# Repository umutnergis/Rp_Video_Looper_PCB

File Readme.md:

# Raspberry Pi Kart Okuma ve Video Oynatma Projesi

Bu proje, Raspberry Pi kullanarak bir kart okuma cihazı USB içinde money.txt klasöründeki int değeri kadar algılandığında USB üzerindeki bir videoyu oynatmayı ve bir fanın çalışmasını kontrol etmeyi amaçlar. Bu README dosyası, projenin nasıl kurulacağı, yapılandırılacağı ve kullanılacağı hakkında temel bilgileri içerir.

## Raspberry Pi için Gereksinimler

Bu projeyi başlatmak için aşağıdaki bileşenlere ihtiyacınız olacak:

- Raspberry Pi (örneğin, Raspberry Pi 3 veya Raspberry Pi 4)
- Kart Okuyucu (USB)
- Fan
- Röle modülü veya sürücü devreleri
- Python 3.7

## Kurulum

1. Raspberry Pi'nizi ağa bağlayın ve gerekli güncellemeleri yapmak için bir terminal açın:

   ```shell
   sudo apt update
   sudo apt upgrade

2. Main.py dosyasını Raspberry Pi'nize yükleyin. 

3. Eğer Raspberry pi'nızda otomatik başlatmak istiyorsanız AutoStart klasöründeki dosyayı inceleyebilirsiniz.

## Raspberry Pi PCB için Gereksinimler

- PCB dosyası Raspberry pi 1B için tasarlanmıştır.
<<<<<<< HEAD

##                                                FOR ENGLİSH

## Raspberry Pi Card Reading and Video Playback Project
 This project aims to use a Raspberry Pi to read a card reader device plugged into a USB port and, when an integer value is detected in the money.txt folder on the USB, play a video from the USB and control the operation of a fan. This README file contains basic information on how to set up, configure, and use the project.

## Requirements for Raspberry Pi
- To start this project, you will need the following components:

## Raspberry Pi (e.g., Raspberry Pi 3 or Raspberry Pi 4)
- Card Reader (USB)
- Fan
- Relay module or driver circuits
- Python 3.7
- Installation

1. Connect your Raspberry Pi to the network and open a terminal to perform the necessary updates:

   ```shell
   sudo apt update
   sudo apt upgrade

2. Upload the Main.py file to your Raspberry Pi.

3. If you want to auto-start the project on your Raspberry Pi, you can review the file in the AutoStart folder.

4. Place the files you want to load into your USB as first.mp4, second.mp4, and money.txt.

## Requirements for Raspberry Pi PCB
- The PCB file is designed for Raspberry Pi 1B.
- KiCAD 7.0 was used for design.
- The required footprints and schematics are available in the "Rp_project_requirements" file.
=======
- KICAD 7.0 kullanılmıştır.
- Gerekli olan footprint ve schematicler "Rp_project_reguirements" dosyasında yüklenmiştir.

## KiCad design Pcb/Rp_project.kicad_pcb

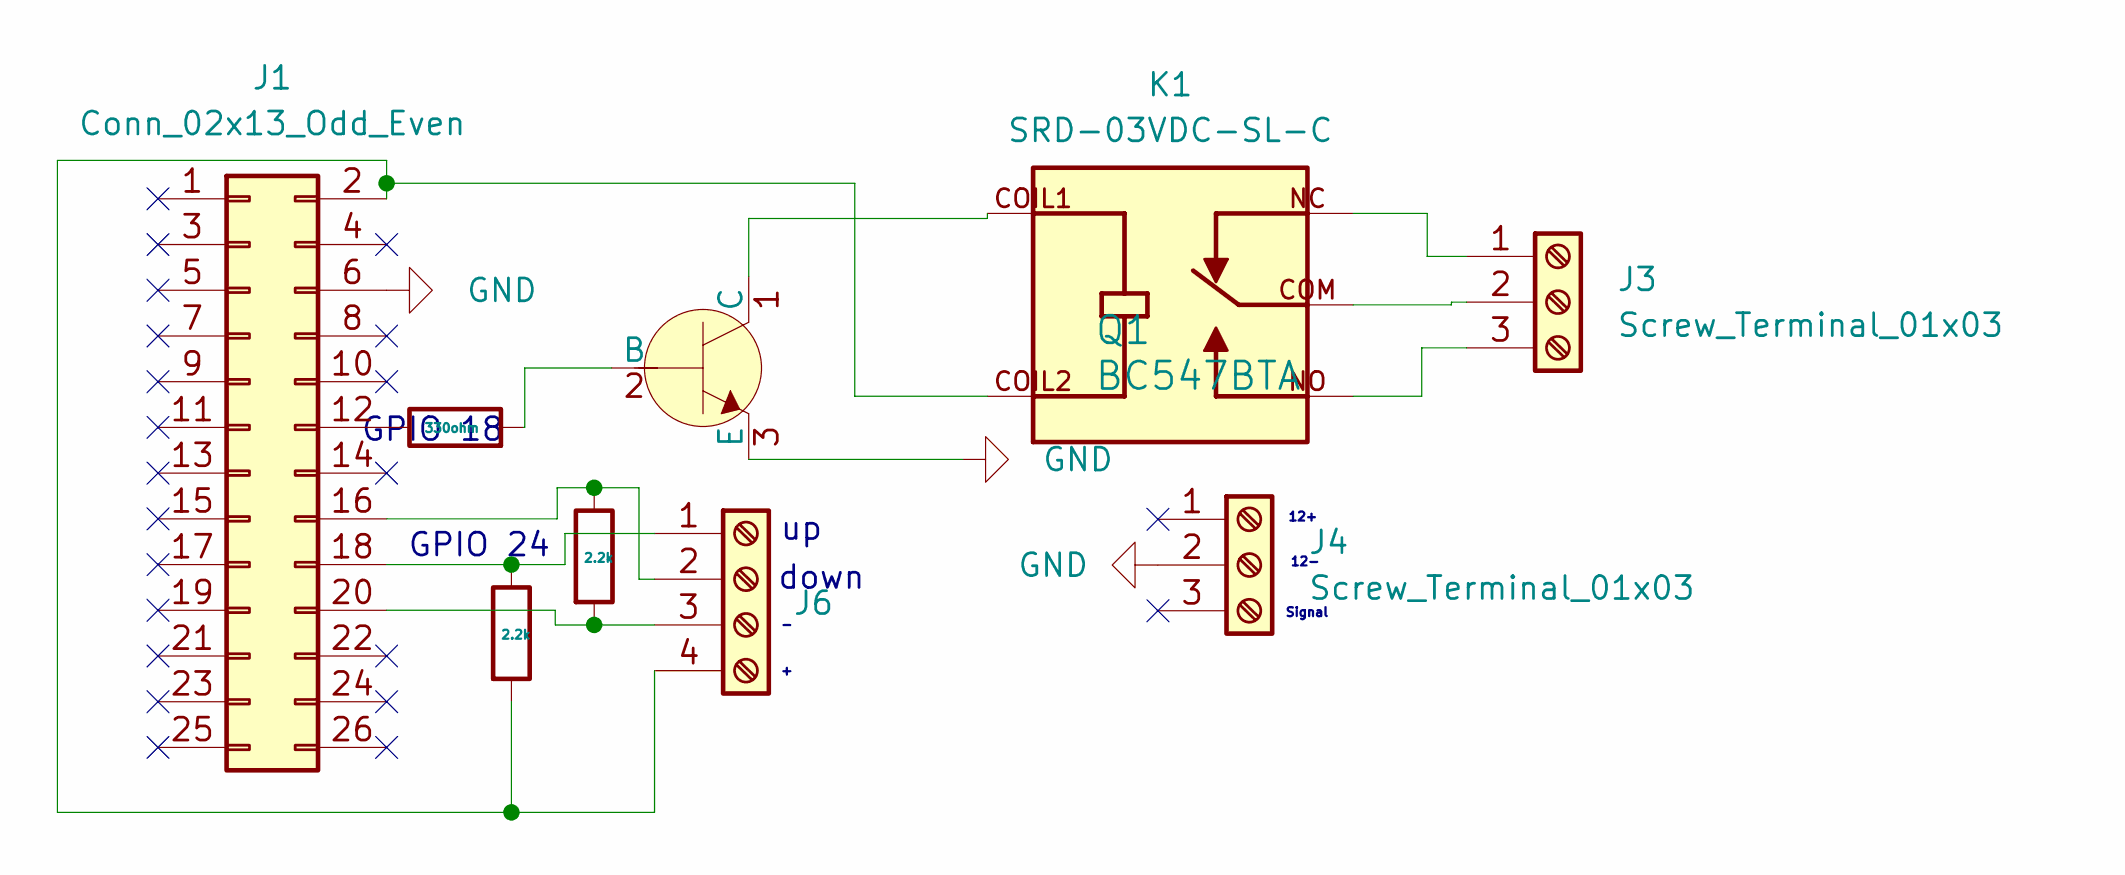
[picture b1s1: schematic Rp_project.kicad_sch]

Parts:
J1: Conn_02x13_Odd_Even; PinSocket_2x13_P2.54mm_Vertical
J3, J4: Screw_Terminal_01x03; TerminalBlock_RND_205-00046_1x03_P5.00mm_Horizontal
J6: Screw_Terminal_01x04; TerminalBlock_RND_205-00047_1x04_P5.00mm_Horizontal
K1: SRD-03VDC-SL-C; RELAY_SRD-03VDC-SL-C; PARTREV 20161104
Q1: BC547BTA; TO-92-3_Formed_Leads; MPN BC547BTA; Digi-Key_PN BC547BTACT-ND
R1, R2: 2.2k; R_Axial_DIN0207_L6.3mm_D2.5mm_P15.24mm_Horizontal
R3: 330ohm; R_Axial_DIN0207_L6.3mm_D2.5mm_P15.24mm_Horizontal

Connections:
GND: J1.6, J4.2, Q1.3 (E)
unnamed: J1.2, J6.4, K1.COIL2, R1.2
unnamed: J1.12, R3.1
unnamed: J1.16, J6.2, R2.1
unnamed: J1.18, J6.1, R1.1
unnamed: J1.20, J6.3, R2.2
unnamed: J3.1, K1.NC
unnamed: J3.2, K1.COM
unnamed: J3.3, K1.NO
unnamed: Q1.2 (B), R3.2
unnamed: K1.COIL1, Q1.1 (C)

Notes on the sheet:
GPIO 18
GPIO 24
down
12+
12-
Signal

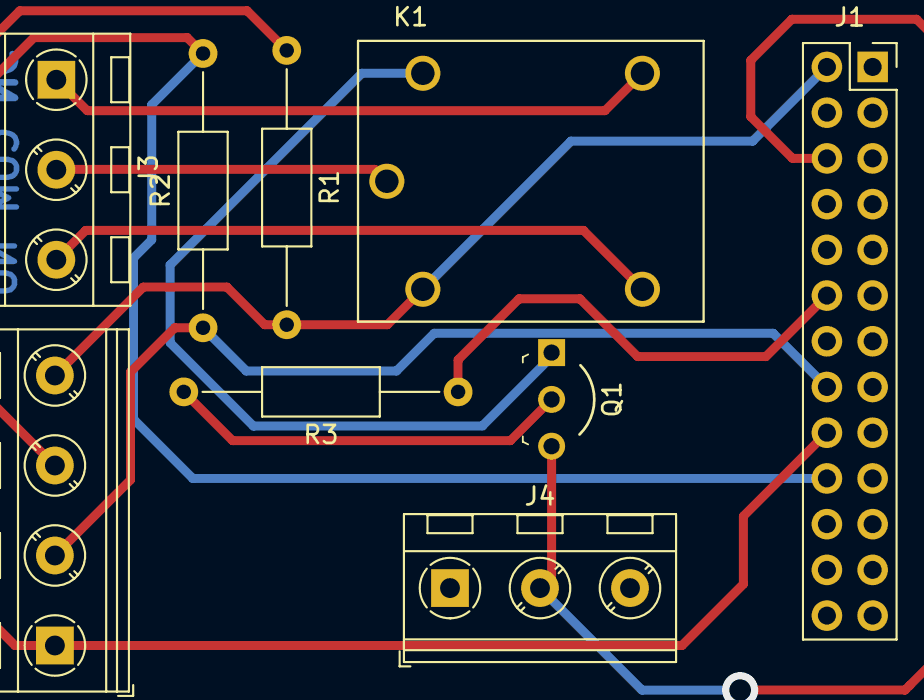
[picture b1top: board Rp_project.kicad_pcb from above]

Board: 2 copper layers, 9 parts (0 on the bottom side), 11 nets.

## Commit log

2023-09-27 Pcb Project Image Uploaded
